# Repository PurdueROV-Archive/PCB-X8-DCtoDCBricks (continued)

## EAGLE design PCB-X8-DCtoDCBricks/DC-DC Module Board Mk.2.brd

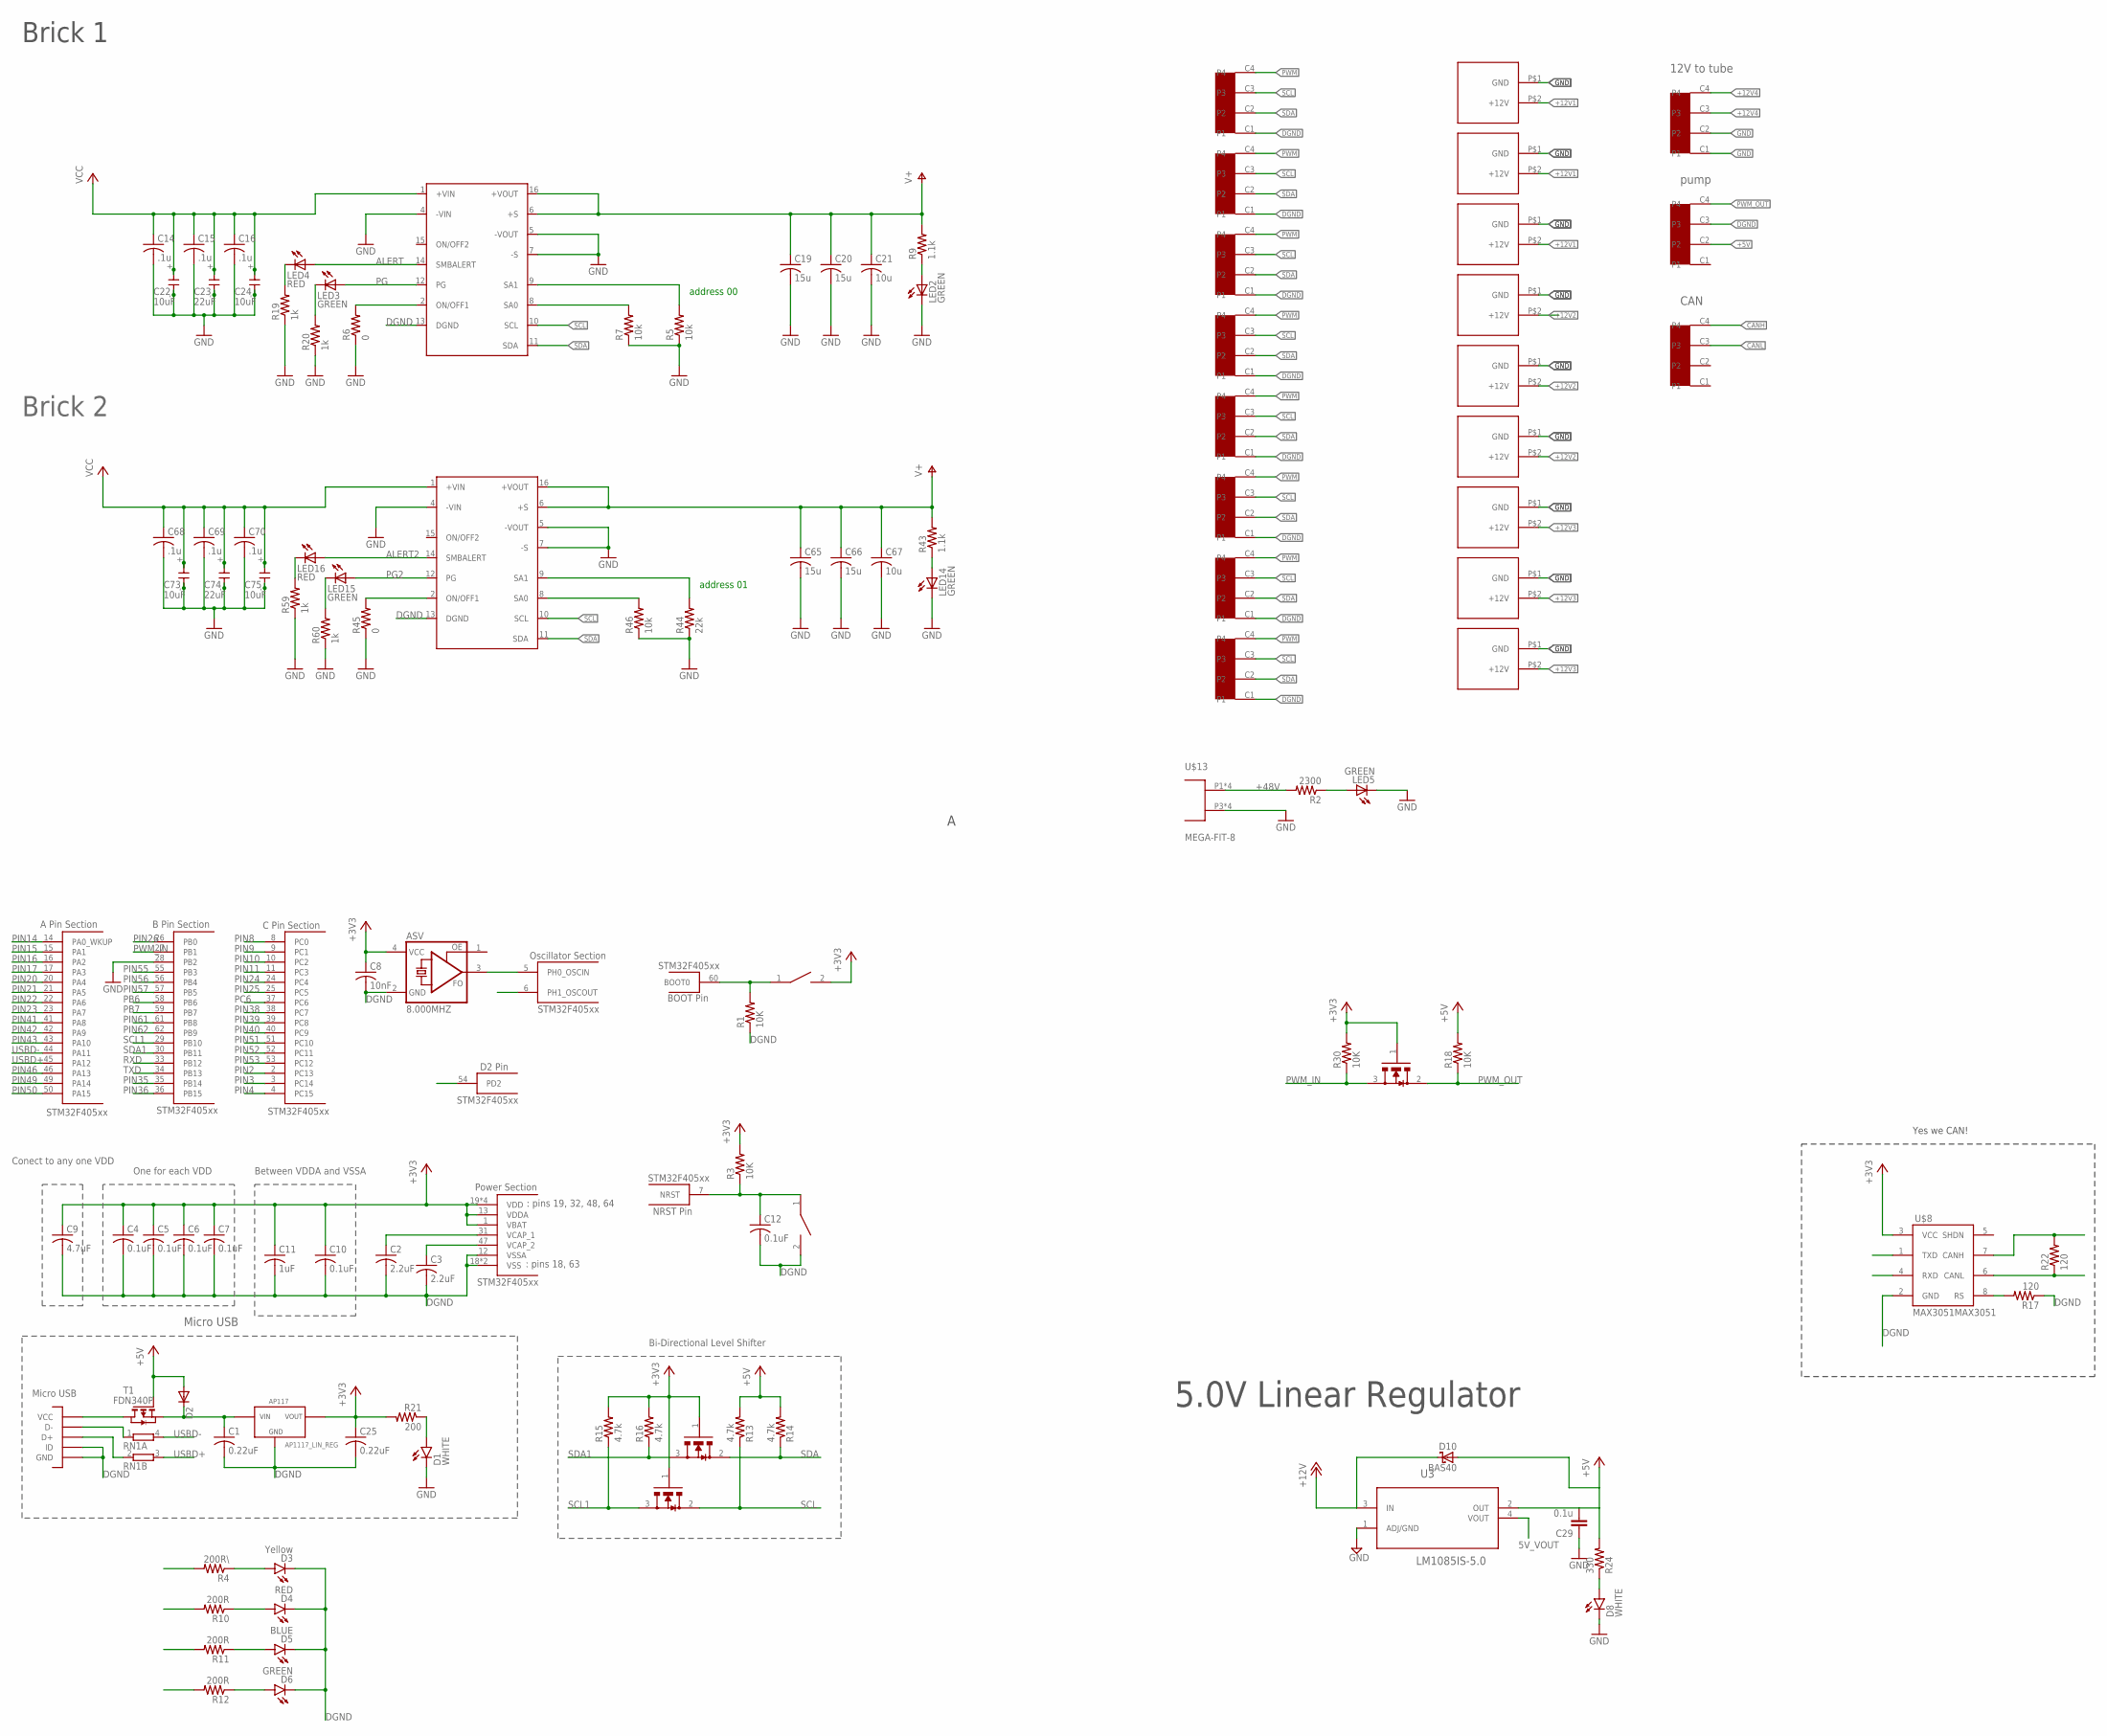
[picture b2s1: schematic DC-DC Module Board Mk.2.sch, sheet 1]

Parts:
ASV: 8.000MHZ; ASF
BSS138: n-chanel mosfet; SOT-23-BSS138
C1, C25: 0.22uF; C0603
C2, C3: 2.2uF; C0603
C4, C5, C6, C7, C10, C12: 0.1uF; C0603
C8: 10nF; C0603
C9: 4.7uF; C0603
C11: 1uF; C0603
C14, C15, C16, C68, C69, C70: .1u; C0603
C19, C20, C65, C66: 15u; C3216
C21, C67: 10u; C0603
C22, C24, C73, C75: 10uF; NICHICON-UX-8X10
C23, C74: 22uF; NICHICON-UX-8X10
C29: 0.1u; C0603
D1, D8: WHITE; LED-1206
D2: DIODE-DO-214AC; DO-214AC
D3: Yellow; LED-0603
D4: RED; LED-0603
D5: BLUE; LED-0603
D6: GREEN; LED-0603
D10: BAS40; SOT23
LED2, LED3, LED5, LED14, LED15: GREEN; LED-0603; PARTNO 160-1446-1-ND
LED4, LED16: RED; LED-0603; PARTNO 160-1446-1-ND
R1, R3, R18, R30: 10K; R0603
R2: 2300; R2512; PARTNO RHC2512FT2K20CT-ND
R4: 200R\; R0603
R5, R7, R46: 10k; R0603; PARTNO 1.00MHCT-ND
R6, R45: 0; R0603; PARTNO 1.00MHCT-ND
R9, R43: 1.1k; R1206; PARTNO RNCP1206FTD1K10CT-ND
R10, R11, R12: 200R; R0603
R13, R14, R15, R16: 4.7k; R0603
R17, R22: 120; R0603
R19, R20, R59, R60: 1k; R0603; PARTNO 1.00MHCT-ND
R21: 200; R0603
R24: 330; R0603
R44: 22k; R0603; PARTNO 1.00MHCT-ND
RN1: 2R-NEXBV4V; EXBV4V
T1: FDN340P; SOT-23
T2: AP1117_LIN_REG; SOT223
U3: LM1085IS-5.0; TO254P1435X457-3N
U$1, U$22: BRICK_DC-DC_CONVERTER
U$2, U$3, U$10, U$11, U$16, U$17, U$18, U$19, U$21: XT60
U$4, U$6: SWITCH; SW_2512
U$5: STM32F405; LQFP64
U$7: MICROUSB; MICRO_B
U$8: MAX3051MAX3051; SOT23-8L
U$9, U$12: BSS138; SOT-23-BSS138
U$13: MEGA-FIT-8
U$15, U$20, U$23, U$24, U$25, U$26, U$27, U$28, U$29, U$30, U$31: MICRO-FIT-4-SMD-HZ

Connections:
5V_VOUT: U3.4 (VOUT)
+3V3: ASV.4 (VCC), BSS138.1 (G), C4.1, C5.1, C6.1, C7.1, C8.1, C9.1, C10.1, C11.1, C25.1, R3.2, R15.2, R16.2, R21.2, R30.2, T2.TAB (VOUT), T2.VOUT, U$4.2, U$5.1 (VBAT), U$5.13 (VDDA), U$5.19 (VDD), U$5.32 (VDD), U$5.48 (VDD), U$5.64 (VDD), U$8.3 (VCC), U$9.1 (G), U$12.1 (G)
+5V: C29.2, D2.A, D10.1 (A), R13.2, R14.2, R18.2, R24.2, T1.3 (G), U3.2 (OUT), U$30.C2 (P2)
+12V: D10.3 (C), U3.3 (IN)
+12V1: C19.1, C20.1, C21.1, R9.2, U$1.6 (+S), U$1.16 (+VOUT), U$2.P$2 (+12V), U$3.P$2 (+12V), U$10.P$2 (+12V)
+12V2: C65.1, C66.1, C67.1, R43.2, U$11.P$2 (+12V), U$16.P$2 (+12V), U$17.P$2 (+12V), U$22.6 (+S), U$22.16 (+VOUT)
+12V3: U$18.P$2 (+12V), U$19.P$2 (+12V), U$21.P$2 (+12V); also elsewhere on the board
+12V4: U$29.C3 (P3), U$29.C4 (P4); also elsewhere on the board
+48V: C14.1, C15.1, C16.1, C22.+, C23.+, C24.+, C68.1, C69.1, C70.1, C73.+, C74.+, C75.+, R2.2, U$1.1 (+VIN), U$13.P1, U$13.P2, U$13.P5, U$13.P6, U$22.1 (+VIN); also elsewhere on the board
ADRS00A: R7.2, U$1.8 (SA0)
ADRS00A4: R46.2, U$22.8 (SA0)
ADRS00B: R5.2, U$1.9 (SA1)
ADRS00B4: R44.2, U$22.9 (SA1)
ALERT: LED4.A, U$1.14 (SMBALERT)
ALERT2: LED16.A, U$22.14 (SMBALERT)
BOOT0: R1.2, U$4.1, U$5.60 (BOOT0)
CANH: R22.2, U$8.7 (CANH), U$31.C4 (P4)
CANL: R22.1, U$8.6 (CANL), U$31.C3 (P3)
DGND: ASV.2 (GND), C1.2, C2.2, C3.2, C4.2, C5.2, C6.2, C7.2, C8.2, C9.2, C10.2, C11.2, C12.2, C25.2, D3.C, D4.C, D5.C, D6.C, R1.1, R17.1, T2.GND, U$1.13 (DGND), U$5.12 (VSSA), U$5.18 (VSS), U$5.63 (VSS), U$6.2, U$7.GND1 (GND), U$7.GND2 (GND), U$7.GND3 (GND), U$7.GND4 (GND), U$7.GND7 (GND), U$7.GND8 (GND), U$7.P4 (ID), U$7.P5 (GND), U$8.2 (GND), U$15.C1 (P1), U$20.C1 (P1), U$22.13 (DGND), U$23.C1 (P1), U$24.C1 (P1), U$25.C1 (P1), U$26.C1 (P1), U$27.C1 (P1), U$28.C1 (P1), U$30.C3 (P3); also elsewhere on the board
GND: C14.2, C15.2, C16.2, C19.2, C20.2, C21.2, C22.-, C23.-, C24.-, C29.1, C65.2, C66.2, C67.2, C68.2, C69.2, C70.2, C73.-, C74.-, C75.-, D1.C, D8.C, LED2.C, LED5.C, LED14.C, R5.1, R6.1, R7.1, R19.1, R20.1, R44.1, R45.1, R46.1, R59.1, R60.1, U3.1 (ADJ/GND), U$1.4 (-VIN), U$1.5 (-VOUT), U$1.7 (-S), U$2.P$1 (GND), U$3.P$1 (GND), U$5.28 (PB2), U$10.P$1 (GND), U$11.P$1 (GND), U$13.P3, U$13.P4, U$13.P7, U$13.P8, U$16.P$1 (GND), U$17.P$1 (GND), U$18.P$1 (GND), U$19.P$1 (GND), U$21.P$1 (GND), U$22.4 (-VIN), U$22.5 (-VOUT), U$22.7 (-S), U$29.C1 (P1), U$29.C2 (P2); also elsewhere on the board
unnamed: R6.2, U$1.2 (ON/OFF1)
unnamed: LED5.A, R2.1
unnamed: LED4.C, R19.2
unnamed: LED3.C, R20.2
unnamed: D1.A, R21.1
unnamed: LED2.A, R9.1
unnamed: RN1.1, U$7.P2 (D-)
unnamed: D8.A, R24.1
unnamed: LED14.A, R43.1
unnamed: RN1.2 (1), U$7.P3 (D+)
unnamed: R45.2, U$22.2 (ON/OFF1)
unnamed: LED16.C, R59.2
unnamed: LED15.C, R60.2
unnamed: T1.1 (D), U$7.P1 (VCC)
unnamed: C1.1, D2.C, T1.2 (S), T2.VIN
unnamed: D3.A, R4.1
unnamed: D4.A, R10.1
unnamed: D5.A, R11.1
unnamed: D6.A, R12.1
unnamed: R17.2, U$8.8 (RS)
NRST: C12.1, R3.1, U$5.7 (NRST), U$6.1
OSCIN: ASV.3 (FO), U$5.5 (PH0_OSCIN)
OSCOUT: U$5.6 (PH1_OSCOUT)
PB6: U$5.58 (PB6)
PB7: U$5.59 (PB7)
PC6: U$5.37 (PC6)
PG: LED3.A, U$1.12 (PG)
PG2: LED15.A, U$22.12 (PG)
PIN2: U$5.2 (PC13)
PIN3: U$5.3 (PC14)
PIN4: U$5.4 (PC15)
PIN8: U$5.8 (PC0)
PIN9: U$5.9 (PC1)
PIN10: U$5.10 (PC2)
PIN11: U$5.11 (PC3)
PIN14: U$5.14 (PA0_WKUP)
PIN15: U$5.15 (PA1)
PIN16: U$5.16 (PA2)
PIN17: U$5.17 (PA3)
PIN20: R4.2, U$5.20 (PA4)
PIN21: R10.2, U$5.21 (PA5)
PIN22: R11.2, U$5.22 (PA6)
PIN23: R12.2, U$5.23 (PA7)
PIN24: U$5.24 (PC4)
PIN25: U$5.25 (PC5)
PIN26: U$5.26 (PB0)
PIN35: U$5.35 (PB14)
PIN36: U$5.36 (PB15)
PIN38: U$5.38 (PC7)
PIN39: U$5.39 (PC8)
PIN40: U$5.40 (PC9)
PIN41: U$5.41 (PA8)
PIN42: U$5.42 (PA9)
PIN43: U$5.43 (PA10)
PIN46: U$5.46 (PA13)
PIN49: U$5.49 (PA14)
PIN50: U$5.50 (PA15)
PIN51: U$5.51 (PC10)
PIN52: U$5.52 (PC11)
PIN53: U$5.53 (PC12)
PIN54: U$5.54 (PD2)
PIN55: U$5.55 (PB3)
PIN56: U$5.56 (PB4)
PIN57: U$5.57 (PB5)
PIN61: U$5.61 (PB8)
PIN62: U$5.62 (PB9)
PWM: U$15.C4 (P4), U$20.C4 (P4), U$23.C4 (P4), U$24.C4 (P4), U$25.C4 (P4), U$26.C4 (P4), U$27.C4 (P4), U$28.C4 (P4)
PWM_IN: R30.1, U$5.27 (PB1), U$12.3 (S)
PWM_OUT: R18.1, U$12.2 (D), U$30.C4 (P4)
RXD: U$5.33 (PB12), U$8.4 (RXD)
SCL: BSS138.2 (D), R13.1, U$1.10 (SCL), U$15.C3 (P3), U$20.C3 (P3), U$22.10 (SCL), U$23.C3 (P3), U$24.C3 (P3), U$25.C3 (P3), U$26.C3 (P3), U$27.C3 (P3), U$28.C3 (P3); also elsewhere on the board
SCL1: BSS138.3 (S), R15.1, U$5.29 (PB10)
SDA: R14.1, U$1.11 (SDA), U$9.2 (D), U$15.C2 (P2), U$20.C2 (P2), U$22.11 (SDA), U$23.C2 (P2), U$24.C2 (P2), U$25.C2 (P2), U$26.C2 (P2), U$27.C2 (P2), U$28.C2 (P2); also elsewhere on the board
SDA1: R16.1, U$5.30 (PB11), U$9.3 (S)
TXD: U$5.34 (PB13), U$8.1 (TXD)
USBD+: RN1.3 (2), U$5.45 (PA12)
USBD-: RN1.4 (2), U$5.44 (PA11)
VCAP_1: C2.1, U$5.31 (VCAP_1)
VCAP_2: C3.1, U$5.47 (VCAP_2)

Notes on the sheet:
address 00
: pins 19, 32, 48, 64
: pins 18, 63
Between VDDA and VSSA
One for each VDD
Conect to any one VDD
Yes we CAN!
Bi-Directional Level Shifter
Brick 1
5.0V Linear Regulator
Brick 2
address 01
Micro USB
12V to tube
pump
CAN

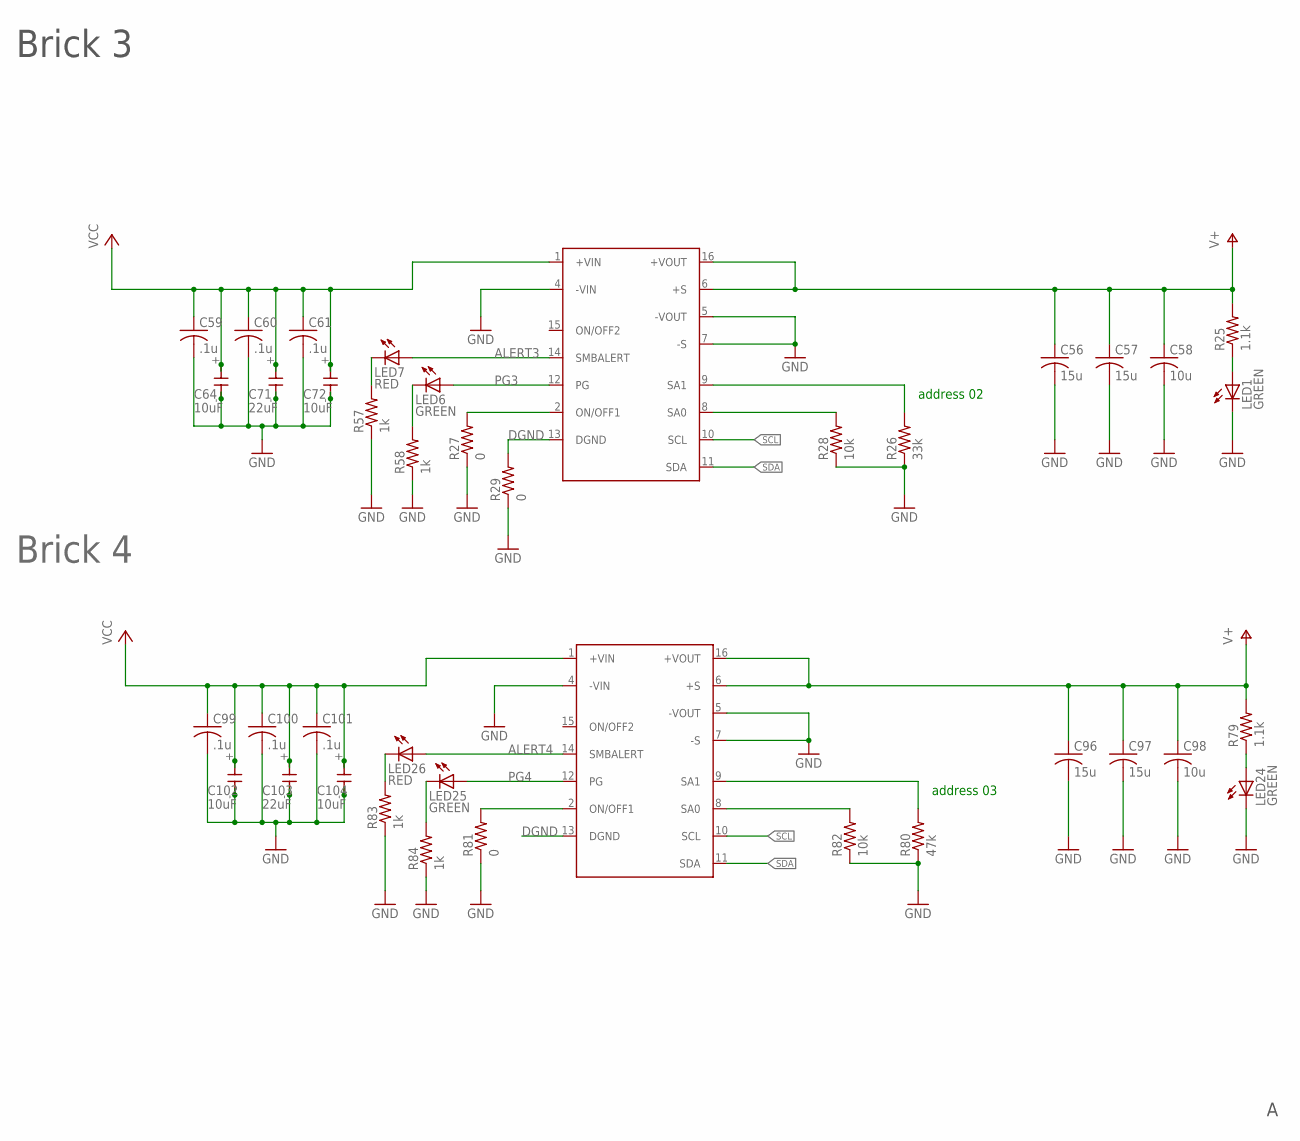
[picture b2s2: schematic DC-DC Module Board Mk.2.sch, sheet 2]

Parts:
C56, C57, C96, C97: 15u; C3216
C58, C98: 10u; C0603
C59, C60, C61, C99, C100, C101: .1u; C0603
C64, C72, C102, C104: 10uF; NICHICON-UX-8X10
C71, C103: 22uF; NICHICON-UX-8X10
LED1, LED6, LED24, LED25: GREEN; LED-0603; PARTNO 160-1446-1-ND
LED7, LED26: RED; LED-0603; PARTNO 160-1446-1-ND
R25, R79: 1.1k; R1206; PARTNO RNCP1206FTD1K10CT-ND
R26: 33k; R0603; PARTNO 1.00MHCT-ND
R27, R29, R81: 0; R0603; PARTNO 1.00MHCT-ND
R28, R82: 10k; R0603; PARTNO 1.00MHCT-ND
R57, R58, R83, R84: 1k; R0603; PARTNO 1.00MHCT-ND
R80: 47k; R0603; PARTNO 1.00MHCT-ND
U$14, U$42: BRICK_DC-DC_CONVERTER

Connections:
+12V3: C56.1, C57.1, C58.1, R25.2, U$14.6 (+S), U$14.16 (+VOUT); also elsewhere on the board
+12V4: C96.1, C97.1, C98.1, R79.2, U$42.6 (+S), U$42.16 (+VOUT); also elsewhere on the board
+48V: C59.1, C60.1, C61.1, C64.+, C71.+, C72.+, C99.1, C100.1, C101.1, C102.+, C103.+, C104.+, U$14.1 (+VIN), U$42.1 (+VIN); also elsewhere on the board
ADRS00A1: R28.2, U$14.8 (SA0)
ADRS00A5: R82.2, U$42.8 (SA0)
ADRS00B1: R26.2, U$14.9 (SA1)
ADRS00B5: R80.2, U$42.9 (SA1)
ALERT3: LED7.A, U$14.14 (SMBALERT)
ALERT4: LED26.A, U$42.14 (SMBALERT)
DGND: R29.2, U$14.13 (DGND), U$42.13 (DGND); also elsewhere on the board
GND: C56.2, C57.2, C58.2, C59.2, C60.2, C61.2, C64.-, C71.-, C72.-, C96.2, C97.2, C98.2, C99.2, C100.2, C101.2, C102.-, C103.-, C104.-, LED1.C, LED24.C, R26.1, R27.1, R28.1, R29.1, R57.1, R58.1, R80.1, R81.1, R82.1, R83.1, R84.1, U$14.4 (-VIN), U$14.5 (-VOUT), U$14.7 (-S), U$42.4 (-VIN), U$42.5 (-VOUT), U$42.7 (-S); also elsewhere on the board
unnamed: LED1.A, R25.1
unnamed: R27.2, U$14.2 (ON/OFF1)
unnamed: LED7.C, R57.2
unnamed: LED6.C, R58.2
unnamed: LED24.A, R79.1
unnamed: R81.2, U$42.2 (ON/OFF1)
unnamed: LED26.C, R83.2
unnamed: LED25.C, R84.2
PG3: LED6.A, U$14.12 (PG)
PG4: LED25.A, U$42.12 (PG)
SCL: U$14.10 (SCL), U$42.10 (SCL); also elsewhere on the board
SDA: U$14.11 (SDA), U$42.11 (SDA); also elsewhere on the board

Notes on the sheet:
address 02
Brick 3
Brick 4
address 03

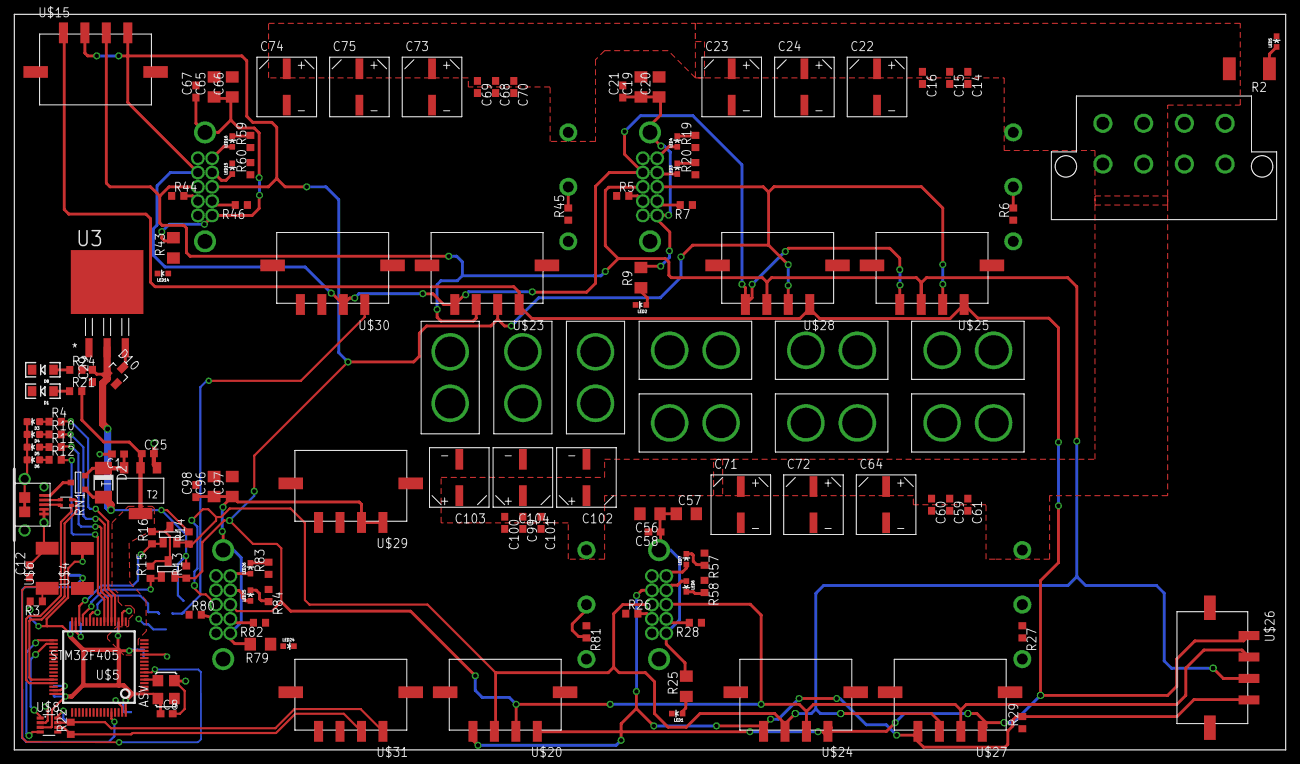
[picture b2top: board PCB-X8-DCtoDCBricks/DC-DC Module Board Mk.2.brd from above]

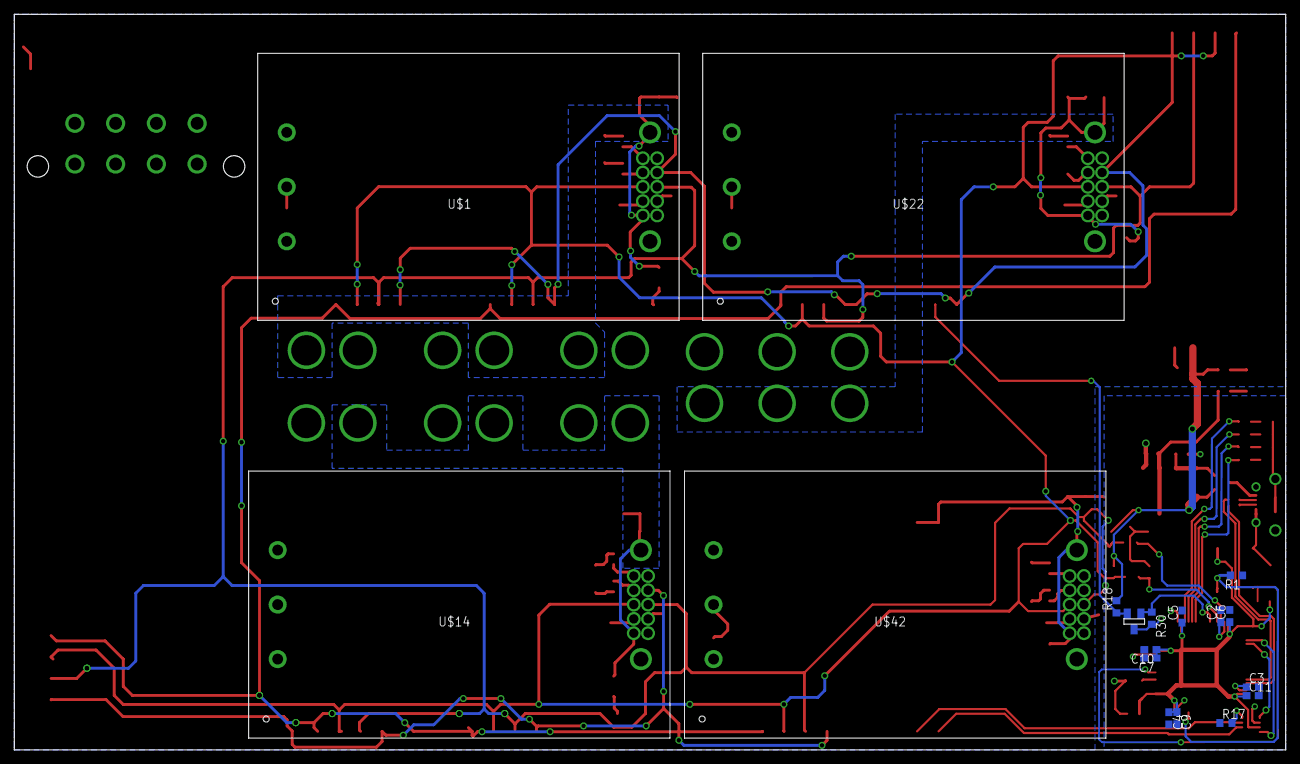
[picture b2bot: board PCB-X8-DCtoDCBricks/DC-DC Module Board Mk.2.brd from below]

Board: 2 copper layers, 177.8 x 102.9 mm, 151 parts (18 on the bottom side), 76 nets.

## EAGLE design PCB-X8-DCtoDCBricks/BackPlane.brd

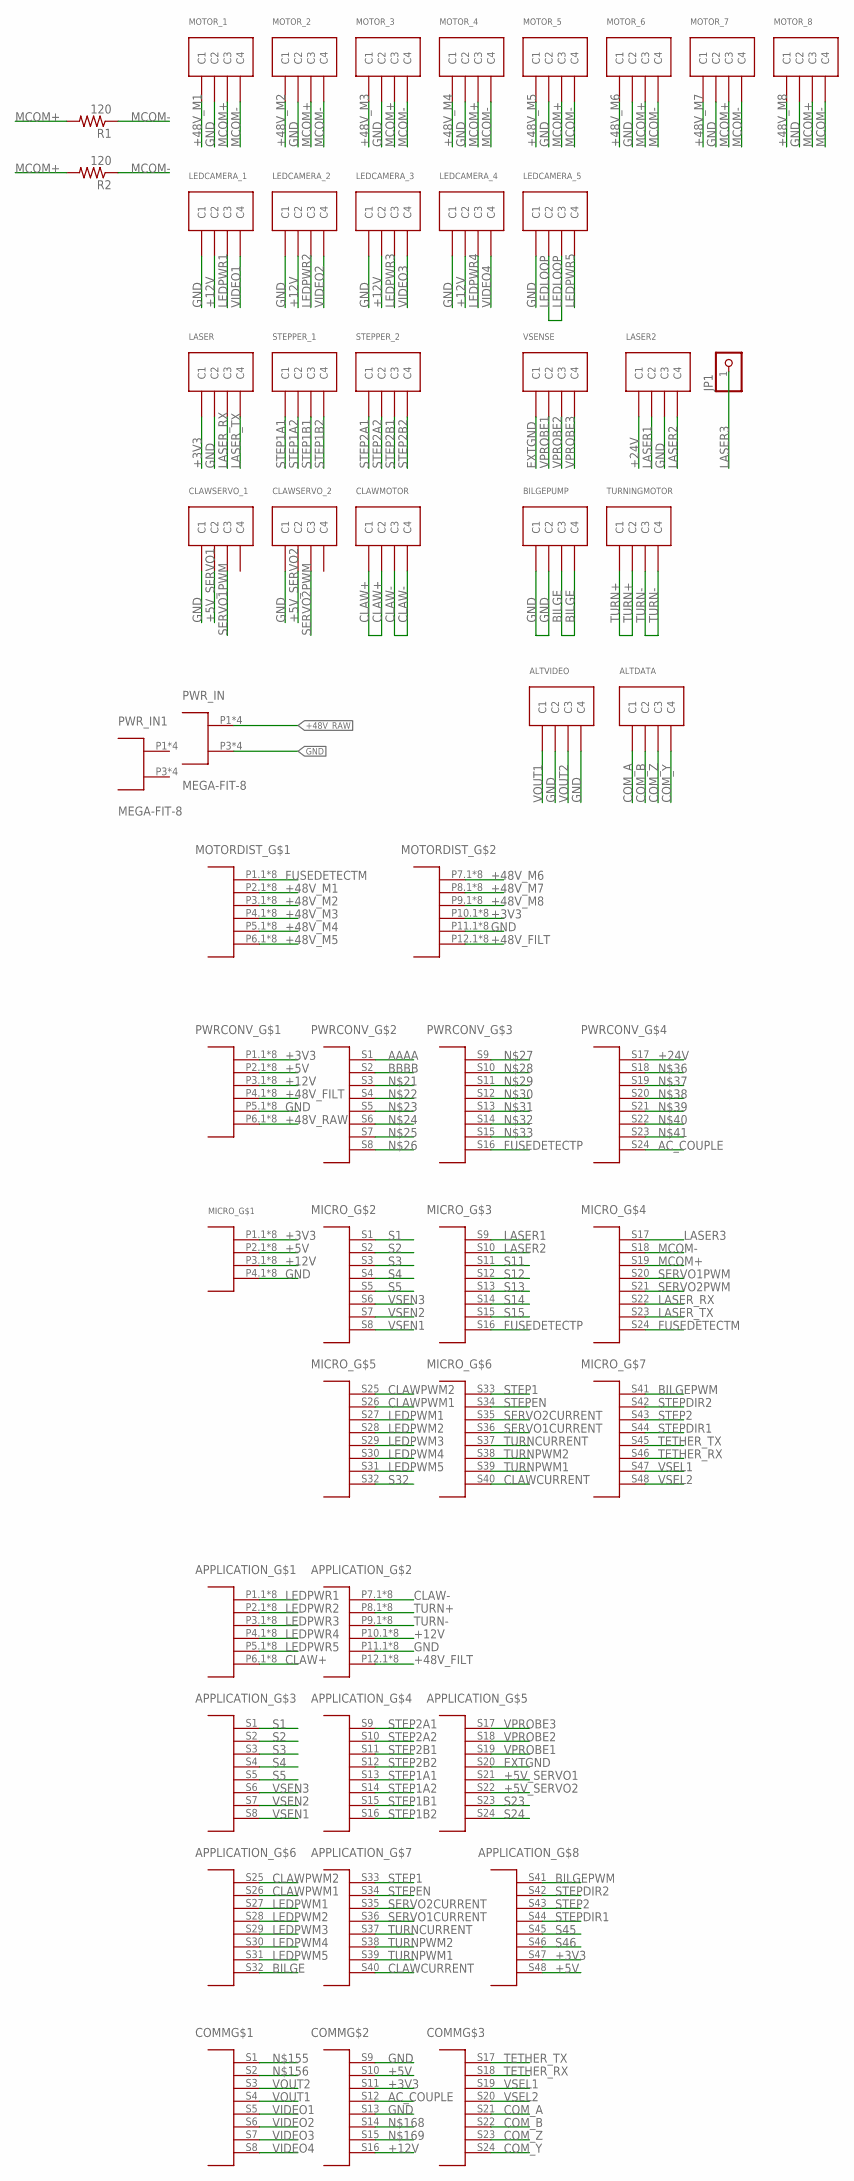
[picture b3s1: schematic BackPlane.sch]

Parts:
ALTDATA: MICRO-FIT-4-SMD-PART; MIRCO-FIT-4-SMD
ALTVIDEO: MICRO-FIT-4-SMD-PART; MIRCO-FIT-4-SMD
APPLICATION_: TEN60-P6-S24-S24-P6-VERT
BILGEPUMP: MICRO-FIT-4-SMD-PART; MIRCO-FIT-4-SMD
CLAWMOTOR: MICRO-FIT-4-SMD-PART; MIRCO-FIT-4-SMD
CLAWSERVO_1, CLAWSERVO_2: MICRO-FIT-4-SMD-PART; MIRCO-FIT-4-SMD
COMM: TEN60-S24-RA
JP1: PINHD-1X1; 1X01
LASER, LASER2: MICRO-FIT-4-SMD-PART; MIRCO-FIT-4-SMD
LEDCAMERA_1, LEDCAMERA_2, LEDCAMERA_3, LEDCAMERA_4, LEDCAMERA_5: MICRO-FIT-4-SMD-PART; MIRCO-FIT-4-SMD
MICRO_: TEN60-S24-S24-P4-VERT
MOTORDIST_: TEN60-P6-P6-VERT
MOTOR_1, MOTOR_2, MOTOR_3, MOTOR_4, MOTOR_5, MOTOR_6, MOTOR_7, MOTOR_8: MICRO-FIT-4-SMD-PART; MIRCO-FIT-4-SMD
PWRCONV_: TEN60-S24-P6-VERT
PWR_IN, PWR_IN1: MEGA-FIT-8
R1, R2: 120; R0603
STEPPER_1, STEPPER_2: MICRO-FIT-4-SMD-PART; MIRCO-FIT-4-SMD
TURNINGMOTOR: MICRO-FIT-4-SMD-PART; MIRCO-FIT-4-SMD
VSENSE: MICRO-FIT-4-SMD-PART; MIRCO-FIT-4-SMD

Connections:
+3V3: APPLICATION_.S47, COMM.S11, LASER.C1, MICRO_.P1.1, MICRO_.P1.2, MICRO_.P1.3, MICRO_.P1.4, MICRO_.P1.5, MICRO_.P1.6, MICRO_.P1.7, MICRO_.P1.8, MOTORDIST_.P10.1, MOTORDIST_.P10.2, MOTORDIST_.P10.3, MOTORDIST_.P10.4, MOTORDIST_.P10.5, MOTORDIST_.P10.6, MOTORDIST_.P10.7, MOTORDIST_.P10.8, PWRCONV_.P1.1, PWRCONV_.P1.2, PWRCONV_.P1.3, PWRCONV_.P1.4, PWRCONV_.P1.5, PWRCONV_.P1.6, PWRCONV_.P1.7, PWRCONV_.P1.8
+5V: APPLICATION_.S48, COMM.S10, MICRO_.P2.1, MICRO_.P2.2, MICRO_.P2.3, MICRO_.P2.4, MICRO_.P2.5, MICRO_.P2.6, MICRO_.P2.7, MICRO_.P2.8, PWRCONV_.P2.1, PWRCONV_.P2.2, PWRCONV_.P2.3, PWRCONV_.P2.4, PWRCONV_.P2.5, PWRCONV_.P2.6, PWRCONV_.P2.7, PWRCONV_.P2.8
+5V_SERVO1: APPLICATION_.S21, CLAWSERVO_1.C2
+5V_SERVO2: APPLICATION_.S22, CLAWSERVO_2.C2
+12V: APPLICATION_.P10.1, APPLICATION_.P10.2, APPLICATION_.P10.3, APPLICATION_.P10.4, APPLICATION_.P10.5, APPLICATION_.P10.6, APPLICATION_.P10.7, APPLICATION_.P10.8, COMM.S16, LEDCAMERA_1.C2, LEDCAMERA_2.C2, LEDCAMERA_3.C2, LEDCAMERA_4.C2, MICRO_.P3.1, MICRO_.P3.2, MICRO_.P3.3, MICRO_.P3.4, MICRO_.P3.5, MICRO_.P3.6, MICRO_.P3.7, MICRO_.P3.8, PWRCONV_.P3.1, PWRCONV_.P3.2, PWRCONV_.P3.3, PWRCONV_.P3.4, PWRCONV_.P3.5, PWRCONV_.P3.6, PWRCONV_.P3.7, PWRCONV_.P3.8
+24V: LASER2.C1, PWRCONV_.S17
+48V_FILT: APPLICATION_.P12.1, APPLICATION_.P12.2, APPLICATION_.P12.3, APPLICATION_.P12.4, APPLICATION_.P12.5, APPLICATION_.P12.6, APPLICATION_.P12.7, APPLICATION_.P12.8, MOTORDIST_.P12.1, MOTORDIST_.P12.2, MOTORDIST_.P12.3, MOTORDIST_.P12.4, MOTORDIST_.P12.5, MOTORDIST_.P12.6, MOTORDIST_.P12.7, MOTORDIST_.P12.8, PWRCONV_.P4.1, PWRCONV_.P4.2, PWRCONV_.P4.3, PWRCONV_.P4.4, PWRCONV_.P4.5, PWRCONV_.P4.6, PWRCONV_.P4.7, PWRCONV_.P4.8
+48V_M1: MOTORDIST_.P2.1, MOTORDIST_.P2.2, MOTORDIST_.P2.3, MOTORDIST_.P2.4, MOTORDIST_.P2.5, MOTORDIST_.P2.6, MOTORDIST_.P2.7, MOTORDIST_.P2.8, MOTOR_1.C1
+48V_M2: MOTORDIST_.P3.1, MOTORDIST_.P3.2, MOTORDIST_.P3.3, MOTORDIST_.P3.4, MOTORDIST_.P3.5, MOTORDIST_.P3.6, MOTORDIST_.P3.7, MOTORDIST_.P3.8, MOTOR_2.C1
+48V_M3: MOTORDIST_.P4.1, MOTORDIST_.P4.2, MOTORDIST_.P4.3, MOTORDIST_.P4.4, MOTORDIST_.P4.5, MOTORDIST_.P4.6, MOTORDIST_.P4.7, MOTORDIST_.P4.8, MOTOR_3.C1
+48V_M4: MOTORDIST_.P5.1, MOTORDIST_.P5.2, MOTORDIST_.P5.3, MOTORDIST_.P5.4, MOTORDIST_.P5.5, MOTORDIST_.P5.6, MOTORDIST_.P5.7, MOTORDIST_.P5.8, MOTOR_4.C1
+48V_M5: MOTORDIST_.P6.1, MOTORDIST_.P6.2, MOTORDIST_.P6.3, MOTORDIST_.P6.4, MOTORDIST_.P6.5, MOTORDIST_.P6.6, MOTORDIST_.P6.7, MOTORDIST_.P6.8, MOTOR_5.C1
+48V_M6: MOTORDIST_.P7.1, MOTORDIST_.P7.2, MOTORDIST_.P7.3, MOTORDIST_.P7.4, MOTORDIST_.P7.5, MOTORDIST_.P7.6, MOTORDIST_.P7.7, MOTORDIST_.P7.8, MOTOR_6.C1
+48V_M7: MOTORDIST_.P8.1, MOTORDIST_.P8.2, MOTORDIST_.P8.3, MOTORDIST_.P8.4, MOTORDIST_.P8.5, MOTORDIST_.P8.6, MOTORDIST_.P8.7, MOTORDIST_.P8.8, MOTOR_7.C1
+48V_M8: MOTORDIST_.P9.1, MOTORDIST_.P9.2, MOTORDIST_.P9.3, MOTORDIST_.P9.4, MOTORDIST_.P9.5, MOTORDIST_.P9.6, MOTORDIST_.P9.7, MOTORDIST_.P9.8, MOTOR_8.C1
+48V_RAW: PWRCONV_.P6.1, PWRCONV_.P6.2, PWRCONV_.P6.3, PWRCONV_.P6.4, PWRCONV_.P6.5, PWRCONV_.P6.6, PWRCONV_.P6.7, PWRCONV_.P6.8, PWR_IN.P1, PWR_IN.P2, PWR_IN.P5, PWR_IN.P6
AAAA: PWRCONV_.S1
AC_COUPLE: COMM.S12, PWRCONV_.S24
BBBB: PWRCONV_.S2
BILGE: APPLICATION_.S32, BILGEPUMP.C3, BILGEPUMP.C4
BILGEPWM: APPLICATION_.S41, MICRO_.S41
CLAW+: APPLICATION_.P6.1, APPLICATION_.P6.2, APPLICATION_.P6.3, APPLICATION_.P6.4, APPLICATION_.P6.5, APPLICATION_.P6.6, APPLICATION_.P6.7, APPLICATION_.P6.8, CLAWMOTOR.C1, CLAWMOTOR.C2
CLAW-: APPLICATION_.P7.1, APPLICATION_.P7.2, APPLICATION_.P7.3, APPLICATION_.P7.4, APPLICATION_.P7.5, APPLICATION_.P7.6, APPLICATION_.P7.7, APPLICATION_.P7.8, CLAWMOTOR.C3, CLAWMOTOR.C4
CLAWCURRENT: APPLICATION_.S40, MICRO_.S40
CLAWPWM1: APPLICATION_.S26, MICRO_.S26
CLAWPWM2: APPLICATION_.S25, MICRO_.S25
COM_A: ALTDATA.C1, COMM.S21
COM_B: ALTDATA.C2, COMM.S22
COM_Y: ALTDATA.C4, COMM.S24
COM_Z: ALTDATA.C3, COMM.S23
EXTGND: APPLICATION_.S20, VSENSE.C1
FUSEDETECTM: MICRO_.S24, MOTORDIST_.P1.1, MOTORDIST_.P1.2, MOTORDIST_.P1.3, MOTORDIST_.P1.4, MOTORDIST_.P1.5, MOTORDIST_.P1.6, MOTORDIST_.P1.7, MOTORDIST_.P1.8
FUSEDETECTP: MICRO_.S16, PWRCONV_.S16
GND: ALTVIDEO.C2, ALTVIDEO.C4, APPLICATION_.P11.1, APPLICATION_.P11.2, APPLICATION_.P11.3, APPLICATION_.P11.4, APPLICATION_.P11.5, APPLICATION_.P11.6, APPLICATION_.P11.7, APPLICATION_.P11.8, BILGEPUMP.C1, BILGEPUMP.C2, CLAWSERVO_1.C1, CLAWSERVO_2.C1, COMM.S9, COMM.S13, LASER.C2, LASER2.C3, LEDCAMERA_1.C1, LEDCAMERA_2.C1, LEDCAMERA_3.C1, LEDCAMERA_4.C1, LEDCAMERA_5.C1, MICRO_.P4.1, MICRO_.P4.2, MICRO_.P4.3, MICRO_.P4.4, MICRO_.P4.5, MICRO_.P4.6, MICRO_.P4.7, MICRO_.P4.8, MOTORDIST_.P11.1, MOTORDIST_.P11.2, MOTORDIST_.P11.3, MOTORDIST_.P11.4, MOTORDIST_.P11.5, MOTORDIST_.P11.6, MOTORDIST_.P11.7, MOTORDIST_.P11.8, MOTOR_1.C2, MOTOR_2.C2, MOTOR_3.C2, MOTOR_4.C2, MOTOR_5.C2, MOTOR_6.C2, MOTOR_7.C2, MOTOR_8.C2, PWRCONV_.P5.1, PWRCONV_.P5.2, PWRCONV_.P5.3, PWRCONV_.P5.4, PWRCONV_.P5.5, PWRCONV_.P5.6, PWRCONV_.P5.7, PWRCONV_.P5.8, PWR_IN.P3, PWR_IN.P4, PWR_IN.P7, PWR_IN.P8
LASER1: LASER2.C2, MICRO_.S9
LASER2: LASER2.C4, MICRO_.S10
LASER3: JP1.1, MICRO_.S17
LASER_RX: LASER.C3, MICRO_.S22
LASER_TX: LASER.C4, MICRO_.S23
LEDLOOP: LEDCAMERA_5.C2, LEDCAMERA_5.C3
LEDPWM1: APPLICATION_.S27, MICRO_.S27
LEDPWM2: APPLICATION_.S28, MICRO_.S28
LEDPWM3: APPLICATION_.S29, MICRO_.S29
LEDPWM4: APPLICATION_.S30, MICRO_.S30
LEDPWM5: APPLICATION_.S31, MICRO_.S31
LEDPWR1: APPLICATION_.P1.1, APPLICATION_.P1.2, APPLICATION_.P1.3, APPLICATION_.P1.4, APPLICATION_.P1.5, APPLICATION_.P1.6, APPLICATION_.P1.7, APPLICATION_.P1.8, LEDCAMERA_1.C3
LEDPWR2: APPLICATION_.P2.1, APPLICATION_.P2.2, APPLICATION_.P2.3, APPLICATION_.P2.4, APPLICATION_.P2.5, APPLICATION_.P2.6, APPLICATION_.P2.7, APPLICATION_.P2.8, LEDCAMERA_2.C3
LEDPWR3: APPLICATION_.P3.1, APPLICATION_.P3.2, APPLICATION_.P3.3, APPLICATION_.P3.4, APPLICATION_.P3.5, APPLICATION_.P3.6, APPLICATION_.P3.7, APPLICATION_.P3.8, LEDCAMERA_3.C3
LEDPWR4: APPLICATION_.P4.1, APPLICATION_.P4.2, APPLICATION_.P4.3, APPLICATION_.P4.4, APPLICATION_.P4.5, APPLICATION_.P4.6, APPLICATION_.P4.7, APPLICATION_.P4.8, LEDCAMERA_4.C3
LEDPWR5: APPLICATION_.P5.1, APPLICATION_.P5.2, APPLICATION_.P5.3, APPLICATION_.P5.4, APPLICATION_.P5.5, APPLICATION_.P5.6, APPLICATION_.P5.7, APPLICATION_.P5.8, LEDCAMERA_5.C4
MCOM+: MICRO_.S19, MOTOR_1.C3, MOTOR_2.C3, MOTOR_3.C3, MOTOR_4.C3, MOTOR_5.C3, MOTOR_6.C3, MOTOR_7.C3, MOTOR_8.C3, R1.2, R2.2
MCOM-: MICRO_.S18, MOTOR_1.C4, MOTOR_2.C4, MOTOR_3.C4, MOTOR_4.C4, MOTOR_5.C4, MOTOR_6.C4, MOTOR_7.C4, MOTOR_8.C4, R1.1, R2.1
S1: APPLICATION_.S1, MICRO_.S1
S2: APPLICATION_.S2, MICRO_.S2
S3: APPLICATION_.S3, MICRO_.S3
S4: APPLICATION_.S4, MICRO_.S4
S5: APPLICATION_.S5, MICRO_.S5
S11: MICRO_.S11
S12: MICRO_.S12
S13: MICRO_.S13
S14: MICRO_.S14
S15: MICRO_.S15
S23: APPLICATION_.S23
S24: APPLICATION_.S24
S32: MICRO_.S32
S45: APPLICATION_.S45
S46: APPLICATION_.S46
SERVO1CURRENT: APPLICATION_.S36, MICRO_.S36
SERVO1PWM: CLAWSERVO_1.C3, MICRO_.S20
SERVO2CURRENT: APPLICATION_.S35, MICRO_.S35
SERVO2PWM: CLAWSERVO_2.C3, MICRO_.S21
STEP1: APPLICATION_.S33, MICRO_.S33
STEP1A1: APPLICATION_.S13, STEPPER_1.C1
STEP1A2: APPLICATION_.S14, STEPPER_1.C2
STEP1B1: APPLICATION_.S15, STEPPER_1.C3
STEP1B2: APPLICATION_.S16, STEPPER_1.C4
STEP2: APPLICATION_.S43, MICRO_.S43
STEP2A1: APPLICATION_.S9, STEPPER_2.C1
STEP2A2: APPLICATION_.S10, STEPPER_2.C2
STEP2B1: APPLICATION_.S11, STEPPER_2.C3
STEP2B2: APPLICATION_.S12, STEPPER_2.C4
STEPDIR1: APPLICATION_.S44, MICRO_.S44
STEPDIR2: APPLICATION_.S42, MICRO_.S42
STEPEN: APPLICATION_.S34, MICRO_.S34
TETHER_RX: COMM.S18, MICRO_.S46
TETHER_TX: COMM.S17, MICRO_.S45
TURN+: APPLICATION_.P8.1, APPLICATION_.P8.2, APPLICATION_.P8.3, APPLICATION_.P8.4, APPLICATION_.P8.5, APPLICATION_.P8.6, APPLICATION_.P8.7, APPLICATION_.P8.8, TURNINGMOTOR.C1, TURNINGMOTOR.C2
TURN-: APPLICATION_.P9.1, APPLICATION_.P9.2, APPLICATION_.P9.3, APPLICATION_.P9.4, APPLICATION_.P9.5, APPLICATION_.P9.6, APPLICATION_.P9.7, APPLICATION_.P9.8, TURNINGMOTOR.C3, TURNINGMOTOR.C4
TURNCURRENT: APPLICATION_.S37, MICRO_.S37
TURNPWM1: APPLICATION_.S39, MICRO_.S39
TURNPWM2: APPLICATION_.S38, MICRO_.S38
VIDEO1: COMM.S5, LEDCAMERA_1.C4
VIDEO2: COMM.S6, LEDCAMERA_2.C4
VIDEO3: COMM.S7, LEDCAMERA_3.C4
VIDEO4: COMM.S8, LEDCAMERA_4.C4
VOUT1: ALTVIDEO.C1, COMM.S4
VOUT2: ALTVIDEO.C3, COMM.S3
VPROBE1: APPLICATION_.S19, VSENSE.C2
VPROBE2: APPLICATION_.S18, VSENSE.C3
VPROBE3: APPLICATION_.S17, VSENSE.C4
VSEL1: COMM.S19, MICRO_.S47
VSEL2: COMM.S20, MICRO_.S48
VSEN1: APPLICATION_.S8, MICRO_.S8
VSEN2: APPLICATION_.S7, MICRO_.S7
VSEN3: APPLICATION_.S6, MICRO_.S6
